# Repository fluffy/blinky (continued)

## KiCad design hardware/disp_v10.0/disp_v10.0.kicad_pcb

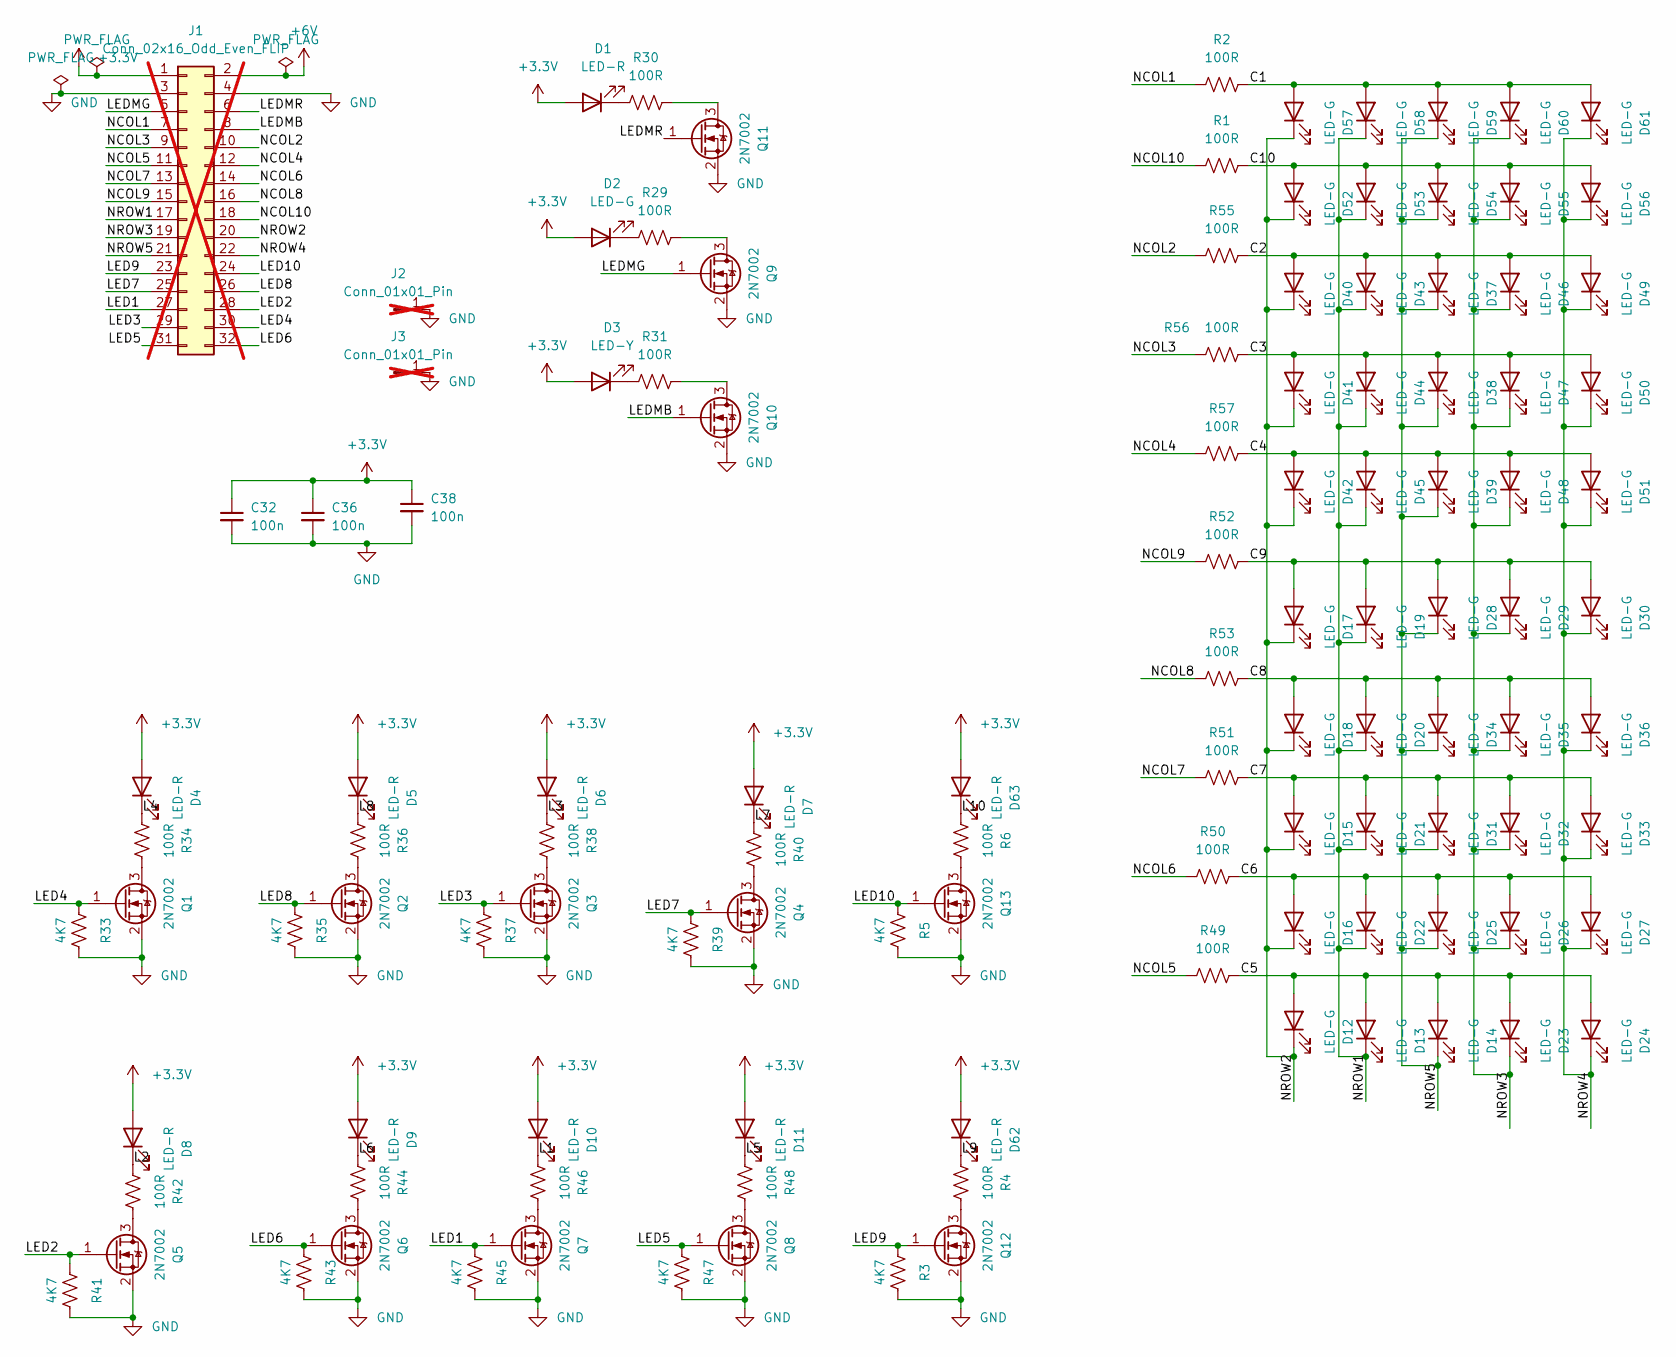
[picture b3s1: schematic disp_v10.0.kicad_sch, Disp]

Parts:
C32, C36, C38: 100n; C_0402_1005Metric; JLCPCB Part # C307331
D1, D4, D5, D6, D7, D8, D9, D10, D11, D62, D63: LED-R; LED_0603_1608Metric; JLCPCB Part # C94869
D2, D12, D13, D14, D15, D16, D17, D18, D19, D20, D21, D22, D23, D24, D25, D26, D27, D28, D29, D30, D31, D32, D33, D34, D35, D36, D37, D38, D39, D40, D41, D42, D43, D44, D45, D46, D47, D48, D49, D50, D51, D52, D53, D54, D55, D56, D57, D58, D59, D60, D61: LED-G; LED_0603_1608Metric; JLCPCB Part # C125093
D3: LED-Y; LED_0603_1608Metric; JLCPCB Part # C72038
J1: Conn_02x16_Odd_Even_FLIP; PinHeader_2x16_P2.54mm_Vertical; not fitted
J2, J3: Conn_01x01_Pin; PinHeader_1x01_P2.54mm_Vertical; not fitted
Q1, Q2, Q3, Q4, Q5, Q6, Q7, Q8, Q9, Q10, Q11, Q12, Q13: 2N7002; SOT-23; JLCPCB Part # C8545
R1, R2, R4, R6, R29, R30, R31, R34, R36, R38, R40, R42, R44, R46, R48, R49, R50, R51, R52, R53, R55, R56, R57: 100R; R_0603_1608Metric; JLCPCB Part # C22775
R3, R5, R33, R35, R37, R39, R41, R43, R45, R47: 4K7; R_0603_1608Metric; JLCPCB Part # C23162

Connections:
+3.3V: C32.1, C36.1, C38.1, D1.2 (A), D2.2 (A), D3.2 (A), D4.2 (A), D5.2 (A), D6.2 (A), D7.2 (A), D8.2 (A), D9.2 (A), D10.2 (A), D11.2 (A), D62.2 (A), D63.2 (A), J1.1
+6V: J1.2
/C1: D57.2 (A), D58.2 (A), D59.2 (A), D60.2 (A), D61.2 (A), R2.1
/C2: D37.2 (A), D40.2 (A), D43.2 (A), D46.2 (A), D49.2 (A), R55.1
/C3: D38.2 (A), D41.2 (A), D44.2 (A), D47.2 (A), D50.2 (A), R56.1
/C4: D39.2 (A), D42.2 (A), D45.2 (A), D48.2 (A), D51.2 (A), R57.1
/C5: D12.2 (A), D13.2 (A), D14.2 (A), D23.2 (A), D24.2 (A), R49.1
/C6: D16.2 (A), D22.2 (A), D25.2 (A), D26.2 (A), D27.2 (A), R50.1
/C7: D15.2 (A), D21.2 (A), D31.2 (A), D32.2 (A), D33.2 (A), R51.1
/C8: D18.2 (A), D20.2 (A), D34.2 (A), D35.2 (A), D36.2 (A), R53.1
/C9: D17.2 (A), D19.2 (A), D28.2 (A), D29.2 (A), D30.2 (A), R52.1
/C10: D52.2 (A), D53.2 (A), D54.2 (A), D55.2 (A), D56.2 (A), R1.1
/L1: D10.1 (K), R46.1
/L2: D8.1 (K), R42.1
/L3: D6.1 (K), R38.1
/L4: D4.1 (K), R34.1
/L5: D11.1 (K), R48.1
/L6: D9.1 (K), R44.1
/L7: D7.1 (K), R40.1
/L8: D5.1 (K), R36.1
/L9: D62.1 (K), R4.1
/L10: D63.1 (K), R6.1
/LED1: J1.27, Q7.1 (G), R45.2
/LED2: J1.28, Q5.1 (G), R41.2
/LED3: J1.29, Q3.1 (G), R37.2
/LED4: J1.30, Q1.1 (G), R33.2
/LED5: J1.31, Q8.1 (G), R47.2
/LED6: J1.32, Q6.1 (G), R43.2
/LED7: J1.25, Q4.1 (G), R39.2
/LED8: J1.26, Q2.1 (G), R35.2
/LED9: J1.23, Q12.1 (G), R3.2
/LED10: J1.24, Q13.1 (G), R5.2
/LEDMB: J1.8, Q10.1 (G)
/LEDMG: J1.5, Q9.1 (G)
/LEDMR: J1.6, Q11.1 (G)
/NCOL1: J1.7, R2.2
/NCOL2: J1.10, R55.2
/NCOL3: J1.9, R56.2
/NCOL4: J1.12, R57.2
/NCOL5: J1.11, R49.2
/NCOL6: J1.14, R50.2
/NCOL7: J1.13, R51.2
/NCOL8: J1.16, R53.2
/NCOL9: J1.15, R52.2
/NCOL10: J1.18, R1.2
/NROW1: D13.1 (K), D19.1 (K), D20.1 (K), D21.1 (K), D22.1 (K), D43.1 (K), D44.1 (K), D45.1 (K), D53.1 (K), D58.1 (K), J1.17
/NROW2: D12.1 (K), D15.1 (K), D16.1 (K), D17.1 (K), D18.1 (K), D40.1 (K), D41.1 (K), D42.1 (K), D52.1 (K), D57.1 (K), J1.20
/NROW3: D23.1 (K), D26.1 (K), D29.1 (K), D32.1 (K), D35.1 (K), D46.1 (K), D47.1 (K), D48.1 (K), D55.1 (K), D60.1 (K), J1.19
/NROW4: D24.1 (K), D27.1 (K), D30.1 (K), D33.1 (K), D36.1 (K), D49.1 (K), D50.1 (K), D51.1 (K), D56.1 (K), D61.1 (K), J1.22
/NROW5: D14.1 (K), D25.1 (K), D28.1 (K), D31.1 (K), D34.1 (K), D37.1 (K), D38.1 (K), D39.1 (K), D54.1 (K), D59.1 (K), J1.21
GND: C32.2, C36.2, C38.2, J1.3, J1.4, J2.1, J3.1, Q1.2 (S), Q2.2 (S), Q3.2 (S), Q4.2 (S), Q5.2 (S), Q6.2 (S), Q7.2 (S), Q8.2 (S), Q9.2 (S), Q10.2 (S), Q11.2 (S), Q12.2 (S), Q13.2 (S), R3.1, R5.1, R33.1, R35.1, R37.1, R39.1, R41.1, R43.1, R45.1, R47.1
unnamed: D1.1 (K), R30.1
unnamed: D2.1 (K), R29.1
unnamed: D3.1 (K), R31.1
unnamed: Q1.3 (D), R34.2
unnamed: Q2.3 (D), R36.2
unnamed: Q3.3 (D), R38.2
unnamed: Q4.3 (D), R40.2
unnamed: Q5.3 (D), R42.2
unnamed: Q6.3 (D), R44.2
unnamed: Q7.3 (D), R46.2
unnamed: Q8.3 (D), R48.2
unnamed: Q9.3 (D), R29.2
unnamed: Q10.3 (D), R31.2
unnamed: Q11.3 (D), R30.2
unnamed: Q12.3 (D), R4.2
unnamed: Q13.3 (D), R6.2

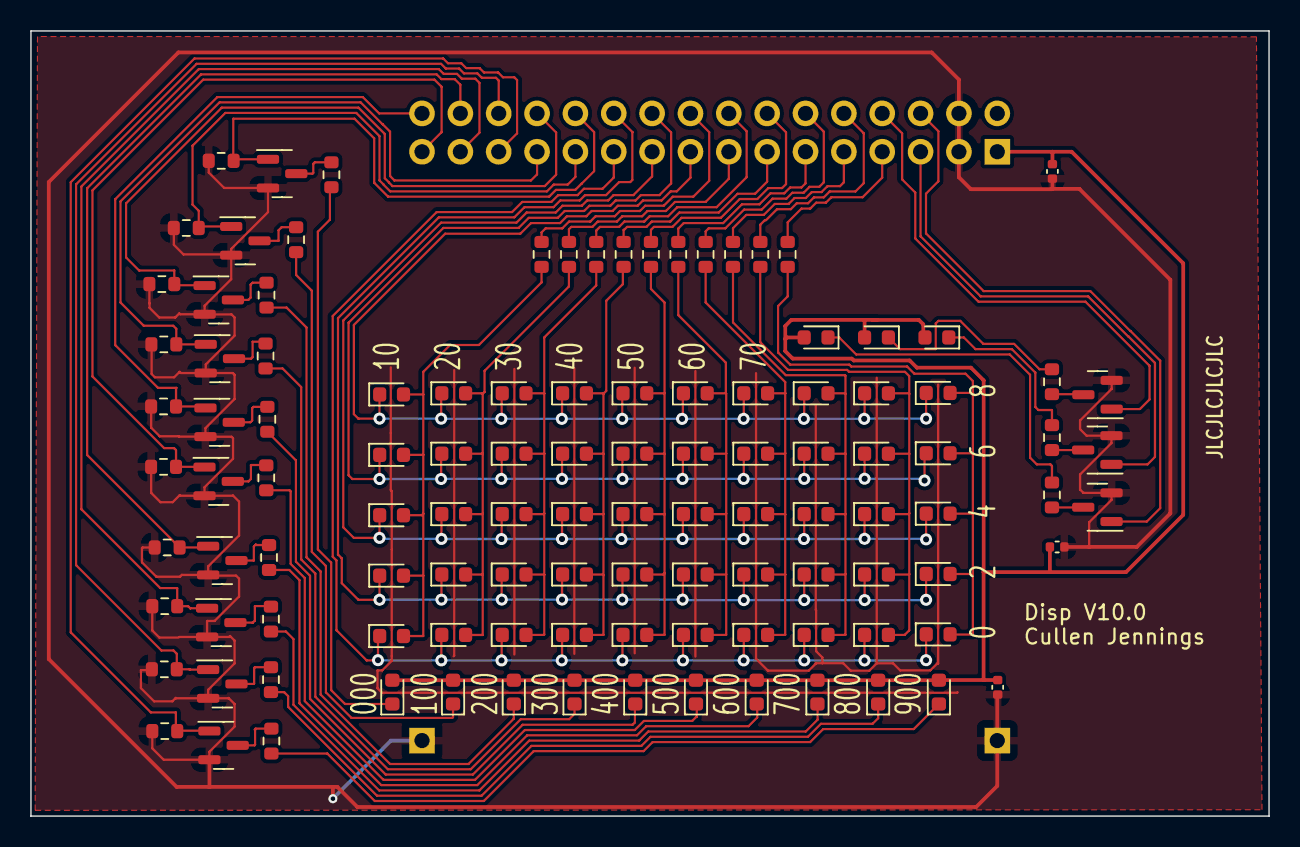
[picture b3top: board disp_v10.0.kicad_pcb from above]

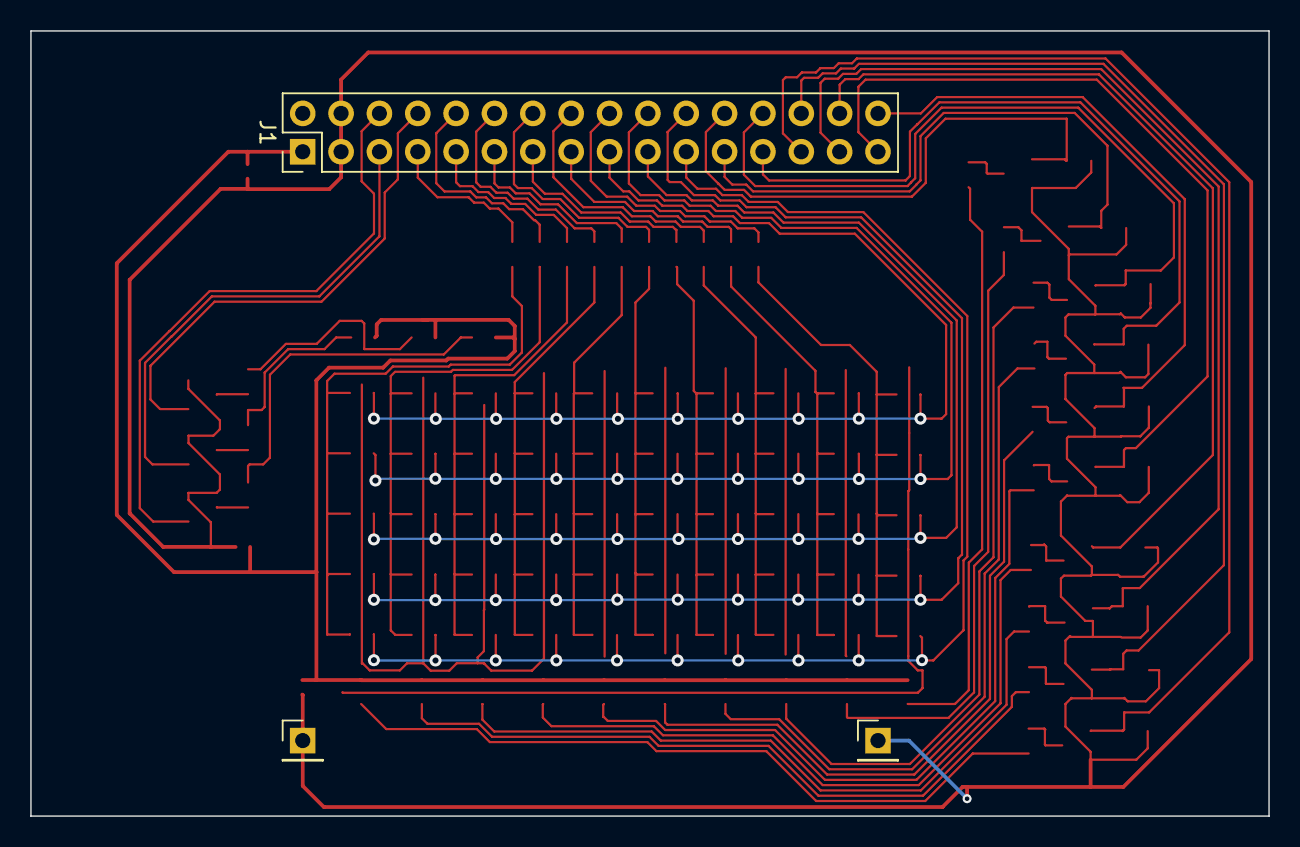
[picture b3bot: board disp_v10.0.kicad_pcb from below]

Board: 2 copper layers, 82.0 x 52.0 mm, 115 parts (3 on the bottom side), 66 nets.

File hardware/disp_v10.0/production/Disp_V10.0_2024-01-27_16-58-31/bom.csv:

Designator,Footprint,Quantity,Value,LCSC Part #
"C32, C36, C38",0402,3,100n,C307331
"D1, D10, D11, D4, D5, D6, D62, D63, D7, D8, D9",0603,11,LED-R,C94869
"D12, D13, D14, D15, D16, D17, D18, D19, D2, D20, D21, D22, D23, D24, D25, D26, D27, D28, D29, D30, D31, D32, D33, D34, D35, D36, D37, D38, D39, D40, D41, D42, D43, D44, D45, D46, D47, D48, D49, D50, D51, D52, D53, D54, D55, D56, D57, D58, D59, D60, D61",0603,51,LED-G,C125093
D3,0603,1,LED-Y,C72038
"Q1, Q10, Q11, Q12, Q13, Q2, Q3, Q4, Q5, Q6, Q7, Q8, Q9",SOT-23,13,2N7002,C8545
"R1, R2, R29, R30, R31, R34, R36, R38, R4, R40, R42, R44, R46, R48, R49, R50, R51, R52, R53, R55, R56, R57, R6",0603,23,100R,C22775
"R3, R33, R35, R37, R39, R41, R43, R45, R47, R5",0603,10,4K7,C23162

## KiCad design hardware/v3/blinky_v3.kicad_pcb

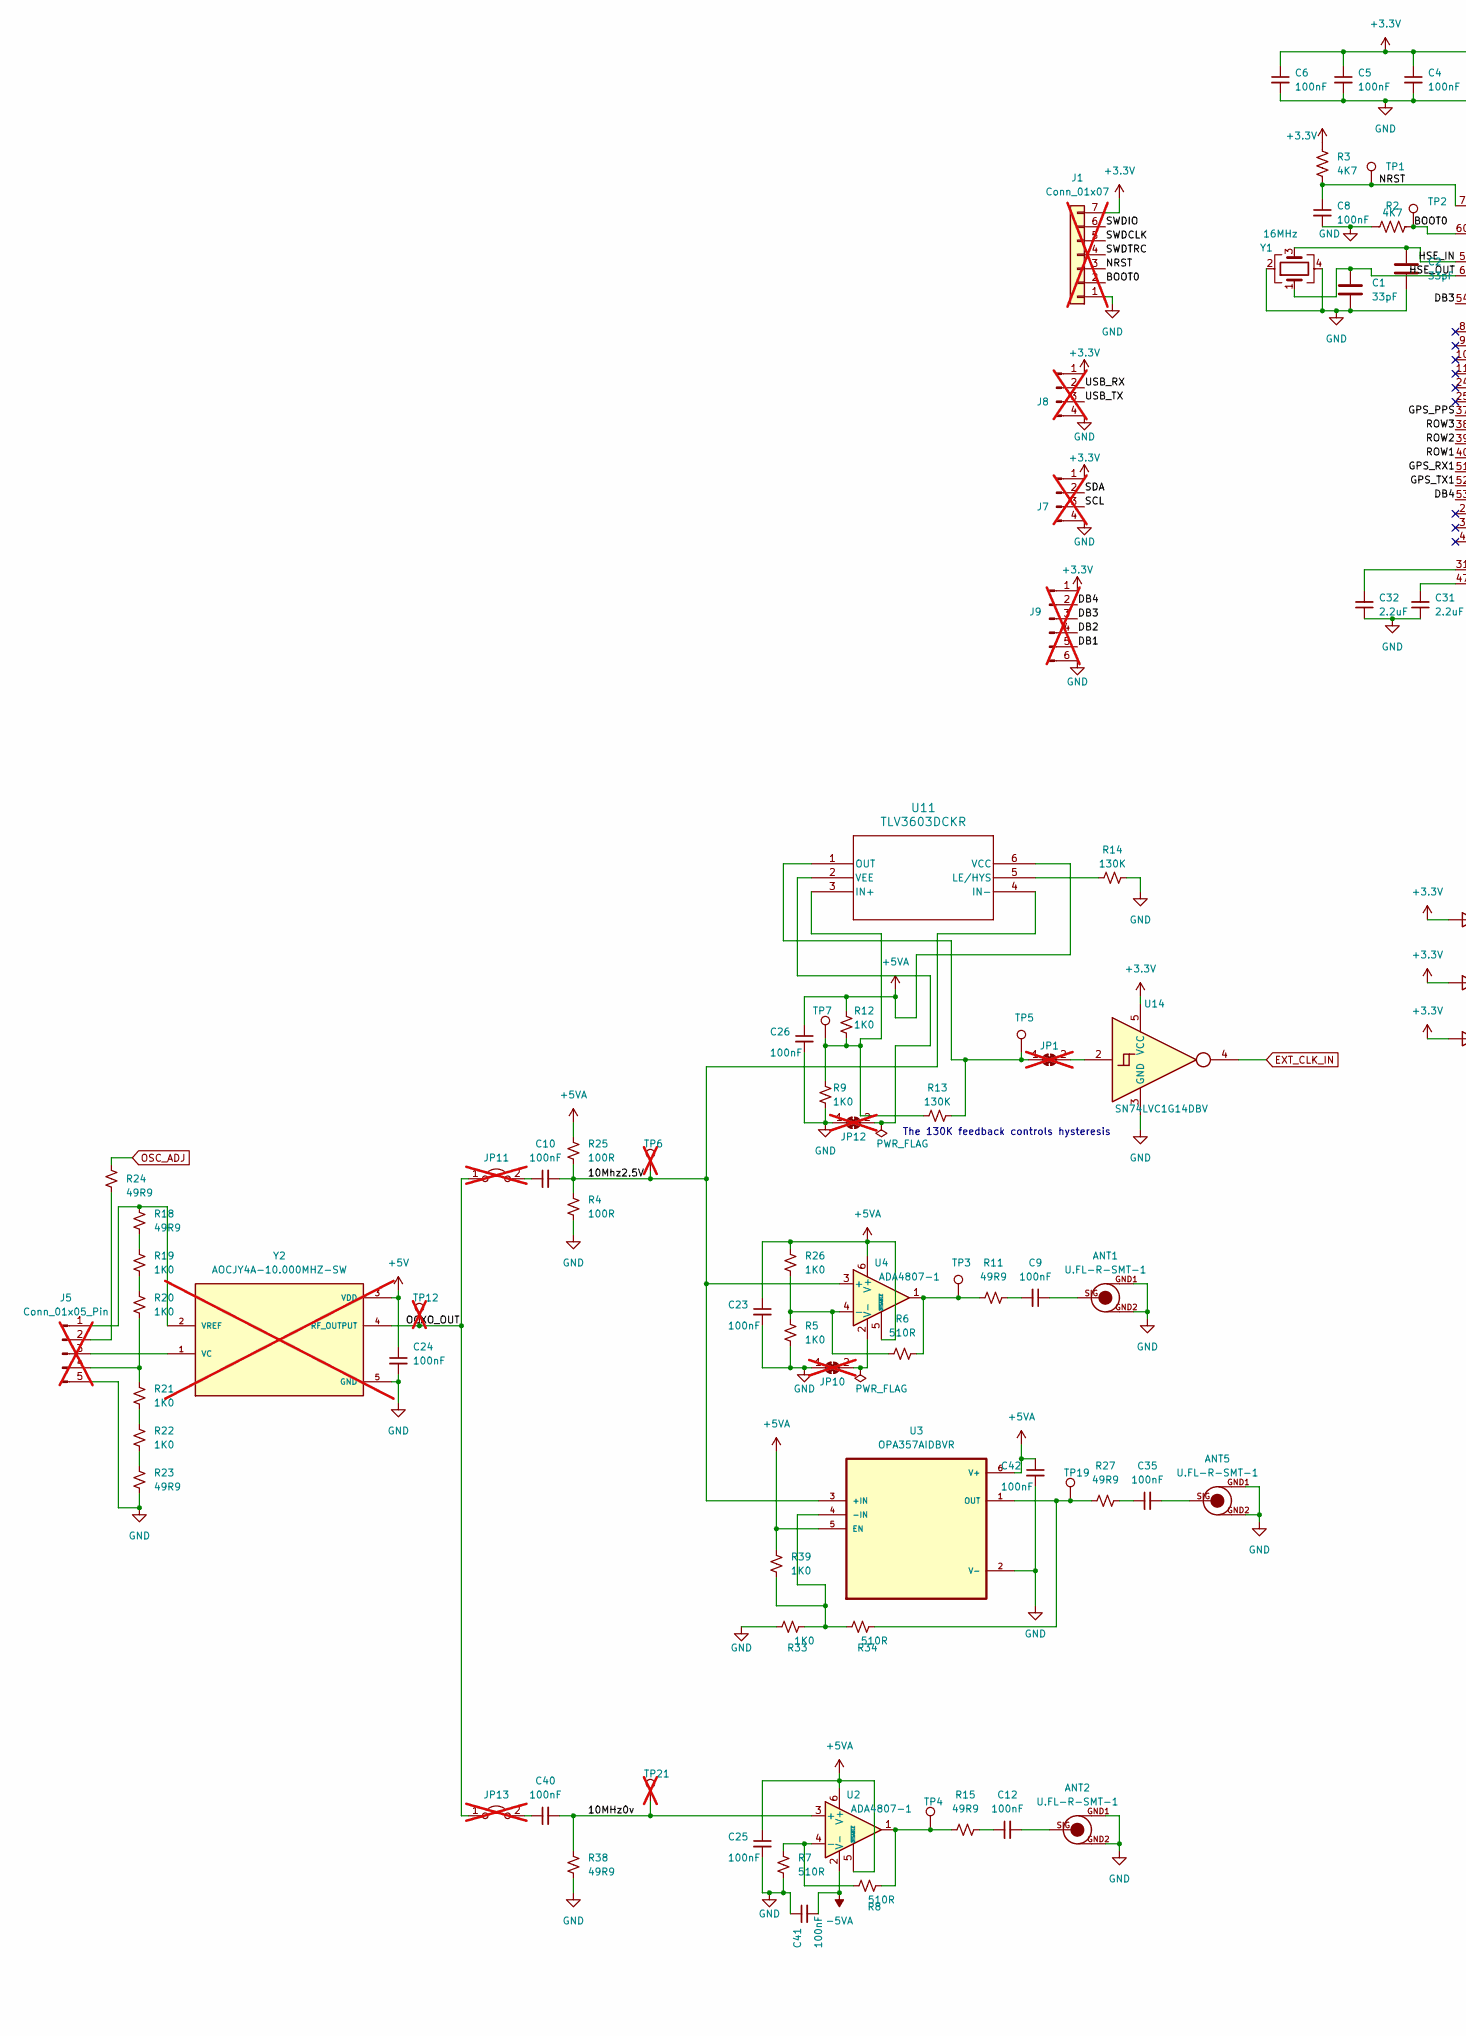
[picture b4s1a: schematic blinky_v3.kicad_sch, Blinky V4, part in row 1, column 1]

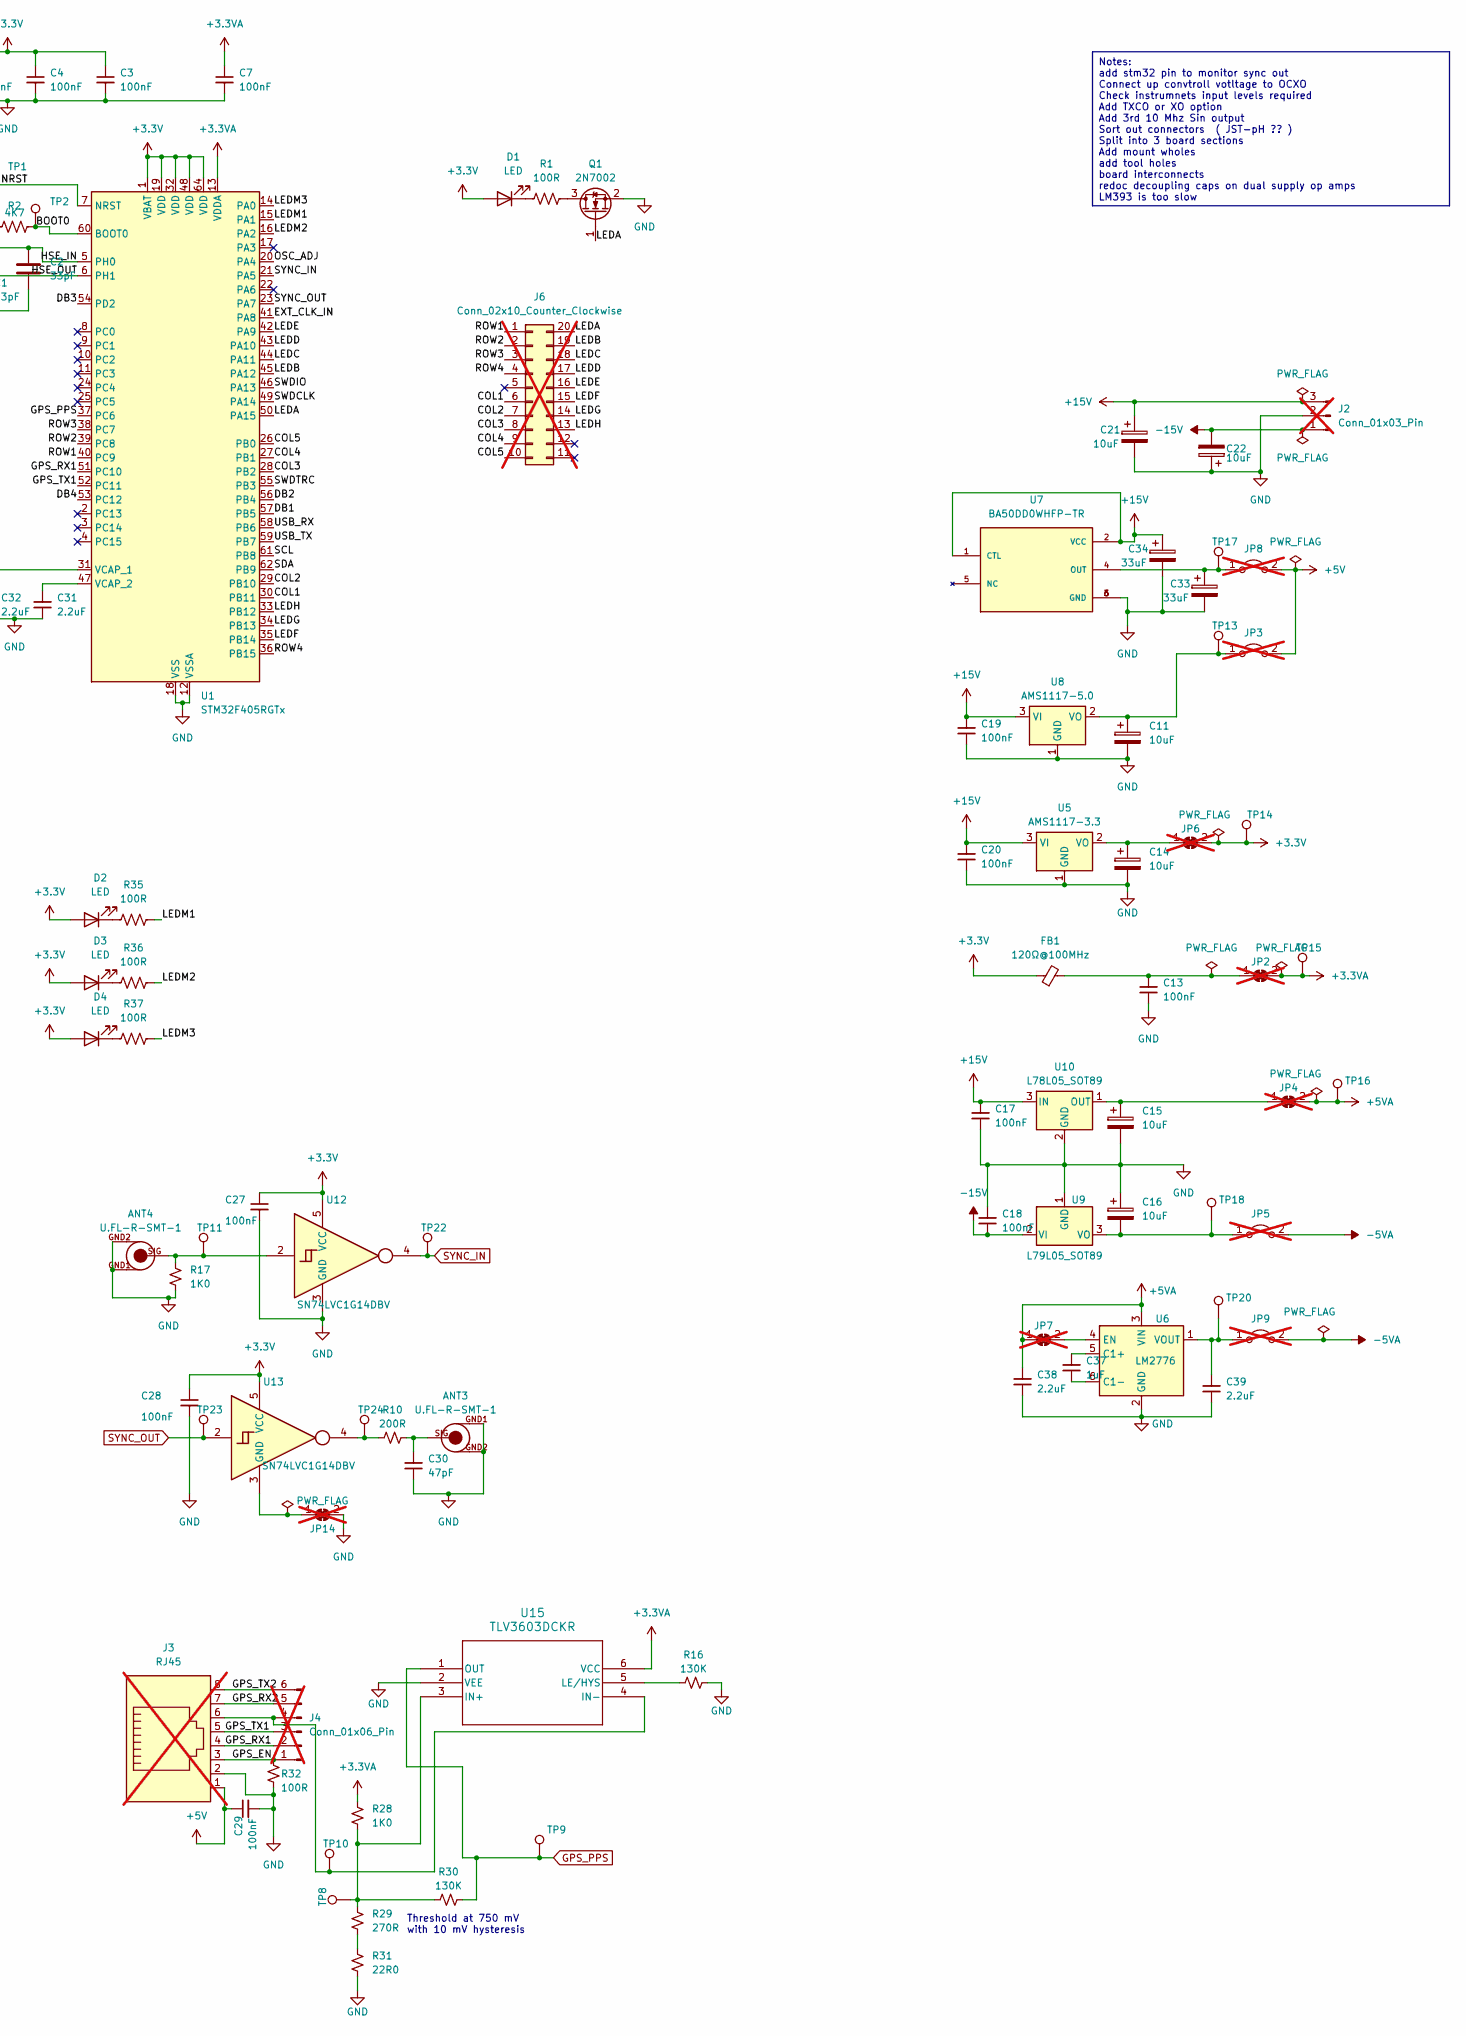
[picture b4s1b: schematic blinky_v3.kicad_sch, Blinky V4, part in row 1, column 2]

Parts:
ANT1, ANT2, ANT3, ANT4, ANT5: U.FL-R-SMT-1; LCSC C88374
C1, C2: 33pF; C_0603_1608Metric; LCSC C1663
C3, C4, C5, C6, C7, C17, C18, C19, C20, C23, C24, C25, C26, C27, C28, C29, C41, C42: 100nF; C_0402_1005Metric; LCSC C307331
C8, C9, C10, C12, C13, C35, C40: 100nF; C_0603_1608Metric; LCSC C14663
C11, C14, C15, C16, C21, C22: 10uF; CP_EIA-3216-18_Kemet-A; LCSC C7171
C30: 47pF; C_0805_2012Metric; LCSC C14857
C31, C32, C38, C39: 2.2uF; C_0603_1608Metric; LCSC C23630
C33, C34: 33uF; CP_EIA-3528-21_Kemet-B; LCSC C128342
C37: 1uF; C_0603_1608Metric; LCSC C15849
D1, D2, D3, D4: LED; R_0603_1608Metric; LCSC C94869
FB1: 120Ω@100MHz; R_0603_1608Metric; LCSC C127301
J1: Conn_01x07; PinHeader_1x07_P2.54mm_Vertical; not fitted
J2: Conn_01x03_Pin; PinHeader_1x03_P2.54mm_Vertical; not fitted
J3: RJ45; RJ45_Amphenol_RJHSE5380; LCSC C464586; not fitted
J4, J9: Conn_01x06_Pin; PinHeader_1x06_P2.54mm_Vertical; not fitted
J5: Conn_01x05_Pin; PinHeader_1x05_P2.54mm_Vertical; not fitted
J6: Conn_02x10_Counter_Clockwise; PinHeader_2x10_P2.54mm_Vertical; not fitted
J7, J8: Conn_01x04_Pin; PinHeader_1x04_P2.54mm_Vertical; not fitted
JP1, JP2, JP4, JP6, JP7, JP10, JP12, JP14: SolderJumper_2_Bridged; SolderJumper-2_P1.3mm_Bridged_RoundedPad1.0x1.5mm; not fitted
JP3, JP5, JP8, JP9, JP11, JP13: TestPoint_2Pads_Pitch2.54mm_Drill0.8mm; not fitted
Q1: 2N7002; SOT-23; LCSC C8545
R1, R4, R25, R32, R35, R36, R37: 100R; R_0603_1608Metric; LCSC C22775
R2, R3: 4K7; R_0603_1608Metric; LCSC C23162
R5, R9, R12, R17, R26, R28, R33, R39: 1K0; R_0603_1608Metric; LCSC C21190
R6, R7, R8, R34: 510R; R_0603_1608Metric; LCSC C23193
R10: 200R; R_0805_2012Metric; LCSC C17540
R11, R15, R18, R23, R24, R27, R38: 49R9; R_0805_2012Metric; LCSC C17720
R13, R14, R16, R30: 130K; R_0603_1608Metric; LCSC C22795
R19, R20, R21, R22: 1K0; R_0805_2012Metric; LCSC C21190
R29: 270R; R_0603_1608Metric; LCSC C22966
R31: 22R0; R_0603_1608Metric; LCSC C23345
TP1, TP2, TP3, TP4, TP5, TP7, TP8, TP9, TP10, TP11, TP13, TP14, TP15, TP16, TP17, TP18, TP19, TP20, TP22, TP23, TP24: TestPoint_THTPad_D1.5mm_Drill0.7mm
TP6, TP12, TP21: TestPoint_THTPad_D1.5mm_Drill0.7mm; not fitted
U1: STM32F405RGTx; LQFP-64_10x10mm_P0.5mm; LCSC C15742
U2, U4: ADA4807-1; SOT-23-6; LCSC C2058411
U3: OPA357AIDBVR; SOT95P280X145-6N; LCSC C139385
U5: AMS1117-3.3; SOT-223-3_TabPin2; LCSC C6186
U6: LM2776; SOT-23-6; LCSC C69527
U7: BA50DD0WHFP-TR; DPAK172P1054X200-6N; PARTREV 003; LCSC C509718
U8: AMS1117-5.0; SOT-223-3_TabPin2; LCSC C6187
U9: L79L05_SOT89; SOT-89-3; LCSC C122849
U10: L78L05_SOT89; SOT-89-3; LCSC C71136
U11, U15: TLV3603DCKR; SC70_DCK_TEX; LCSC C5213955
U12, U13, U14: SN74LVC1G14DBV; SOT-23-5; LCSC C133145
Y1: 16MHz; Crystal_SMD_3225-4Pin_3.2x2.5mm; LCSC C13738
Y2: AOCJY4A-10.000MHZ-SW; XTAL_AOCJY4A-10.000MHZ-SW; PARTREV 07.24.11; LCSC C1670487; not fitted

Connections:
+3.3V: C3.1, C4.1, C5.1, C6.1, C27.1, C28.1, D1.2 (A), D2.2 (A), D3.2 (A), D4.2 (A), FB1.1, J1.7, J7.1, J8.1, J9.1, JP6.2 (B), R3.1, TP14.1, U1.1 (VBAT), U1.19 (VDD), U1.32 (VDD), U1.48 (VDD), U1.64 (VDD), U12.5 (VCC), U13.5 (VCC), U14.5 (VCC)
+3.3VA: C7.1, JP2.2 (B), R28.1, TP15.1, U1.13 (VDDA), U15.6 (VCC)
+5V: C24.1, C29.1, J3.1, JP3.2 (B), JP8.2 (B), Y2.3 (VDD)
+5VA: C23.1, C25.1, C26.1, C38.2, C42.1, JP4.2 (B), JP7.1 (A), R12.1, R25.1, R26.1, R39.1, TP16.1, U2.5 (~DISABLE), U2.6 (V+), U3.5 (EN), U3.6 (V+), U4.5 (~DISABLE), U4.6 (V+), U6.3 (VIN), U11.6 (VCC)
+15V: C17.2, C19.2, C20.2, C21.1, C34.1, J2.3, U5.3 (VI), U7.1 (CTL), U7.2 (VCC), U8.3 (VI), U10.3 (IN)
-5VA: C41.2, JP5.2 (B), JP9.2 (B), U2.2 (V-)
-15V: C18.1, C22.2, J2.1, U9.2 (VI)
/10MHz0v: C40.2, R38.1, TP21.1, U2.3 (+)
/10Mhz2.5V: C10.2, R4.1, R25.2, TP6.1, U3.3 (+IN), U4.3 (+), U11.4 (IN-)
/BOOT0: J1.2, R2.1, TP2.1, U1.60 (BOOT0)
/COL1: J6.6, U1.30 (PB11)
/COL2: J6.7, U1.29 (PB10)
/COL3: J6.8, U1.28 (PB2)
/COL4: J6.9, U1.27 (PB1)
/COL5: J6.10, U1.26 (PB0)
/DB1: J9.5, U1.57 (PB5)
/DB2: J9.4, U1.56 (PB4)
/DB3: J9.3, U1.54 (PD2)
/DB4: J9.2, U1.53 (PC12)
/GPS_EN: J3.3, J4.1, R32.1
/GPS_RX1: J3.4, J4.2, U1.51 (PC10)
/GPS_RX2: J3.7, J4.5
/GPS_TX1: J3.5, J4.3, U1.52 (PC11)
/GPS_TX2: J3.8, J4.6
/HSE_IN: C2.1, U1.5 (PH0), Y1.3
/HSE_OUT: C1.1, U1.6 (PH1), Y1.1
/LEDA: J6.20, Q1.1 (G), U1.50 (PA15)
/LEDB: J6.19, U1.45 (PA12)
/LEDC: J6.18, U1.44 (PA11)
/LEDD: J6.17, U1.43 (PA10)
/LEDE: J6.16, U1.42 (PA9)
/LEDF: J6.15, U1.35 (PB14)
/LEDG: J6.14, U1.34 (PB13)
/LEDH: J6.13, U1.33 (PB12)
/LEDM1: R35.2, U1.15 (PA1)
/LEDM2: R36.2, U1.16 (PA2)
/LEDM3: R37.2, U1.14 (PA0)
/NRST: C8.1, J1.3, R3.2, TP1.1, U1.7 (NRST)
/OCXO_OUT: JP11.1 (A), JP13.1 (A), TP12.1, Y2.4 (RF_OUTPUT)
/ROW1: J6.1, U1.40 (PC9)
/ROW2: J6.2, U1.39 (PC8)
/ROW3: J6.3, U1.38 (PC7)
/ROW4: J6.4, U1.36 (PB15)
/SCL: J7.3, U1.61 (PB8)
/SDA: J7.2, U1.62 (PB9)
/SWDCLK: J1.5, U1.49 (PA14)
/SWDIO: J1.6, U1.46 (PA13)
/SWDTRC: J1.4, U1.55 (PB3)
/USB_RX: J8.2, U1.58 (PB6)
/USB_TX: J8.3, U1.59 (PB7)
EXT_CLK_IN: U1.41 (PA8), U14.4
GND: ANT1.GND1, ANT1.GND2, ANT2.GND1, ANT2.GND2, ANT3.GND1, ANT3.GND2, ANT4.GND1, ANT4.GND2, ANT5.GND1, ANT5.GND2, C1.2, C2.2, C3.2, C4.2, C5.2, C6.2, C7.2, C8.2, C11.2, C13.1, C14.2, C15.2, C16.1, C17.1, C18.2, C19.1, C20.1, C21.2, C22.1, C23.2, C24.2, C25.2, C26.2, C27.2, C28.2, C29.2, C30.1, C31.1, C32.1, C33.2, C34.2, C38.1, C39.1, C41.1, C42.2, J1.1, J2.2, J3.2, J5.5, J7.4, J8.4, J9.6, JP10.1 (A), JP12.1 (A), JP14.2 (B), Q1.2 (S), R2.2, R4.2, R5.2, R7.2, R9.2, R14.2, R16.2, R17.2, R23.2, R31.2, R32.2, R33.1, R38.2, U1.12 (VSSA), U1.18 (VSS), U1.63 (VSS), U3.2 (V-), U5.1 (GND), U6.2 (GND), U7.3 (GND), U7.6 (GND), U8.1 (GND), U9.1 (GND), U10.2 (GND), U12.3 (GND), U14.3 (GND), U15.2 (VEE), Y1.2, Y1.4, Y2.5 (GND)
GPS_PPS: R30.2, TP9.1, U1.37 (PC6), U15.1 (OUT)
unnamed: ANT1.SIG, C9.1
unnamed: ANT2.SIG, C12.2
unnamed: ANT3.SIG, C30.2, R10.2
unnamed: ANT4.SIG, R17.1, TP11.1, U12.2
unnamed: ANT5.SIG, C35.2
unnamed: C9.2, R11.2
unnamed: C12.1, R15.2
unnamed: C35.1, R27.2
unnamed: D1.1 (K), R1.1
unnamed: D2.1 (K), R35.1
unnamed: D3.1 (K), R36.1
unnamed: D4.1 (K), R37.1
unnamed: J3.6, J4.4, TP10.1, U15.4 (IN-)
unnamed: J5.1, R18.1, Y2.2 (VREF)
unnamed: J5.2, R24.2
unnamed: J5.3, Y2.1 (VC)
unnamed: J5.4, R20.2, R21.1
unnamed: JP1.1 (A), R13.2, TP5.1, U11.1 (OUT)
unnamed: JP1.2 (B), U14.2
unnamed: C13.2, FB1.2, JP2.1 (A)
unnamed: C11.1, JP3.1 (A), TP13.1, U8.2 (VO)
unnamed: C15.1, JP4.1 (A), U10.1 (OUT)
unnamed: C16.2, JP5.1 (A), TP18.1, U9.3 (VO)
unnamed: C14.1, JP6.1 (A), U5.2 (VO)
unnamed: JP7.2 (B), U6.4 (EN)
unnamed: C33.1, JP8.1 (A), TP17.1, U7.4 (OUT)
unnamed: C39.2, JP9.1 (A), TP20.1, U6.1 (VOUT)
unnamed: JP10.2 (B), U4.2 (V-)
unnamed: C10.1, JP11.2 (B)
unnamed: JP12.2 (B), U11.2 (VEE)
unnamed: C40.1, JP13.2 (B)
unnamed: JP14.1 (A), U13.3 (GND)
unnamed: Q1.3 (D), R1.2
unnamed: R10.1, TP24.1, U13.4
unnamed: R6.2, R11.1, TP3.1, U4.1
unnamed: R8.2, R15.1, TP4.1, U2.1
unnamed: R18.2, R19.1
unnamed: R19.2, R20.1
unnamed: R21.2, R22.1
unnamed: R22.2, R23.1
unnamed: R29.2, R31.1
unnamed: C32.2, U1.31 (VCAP_1)
unnamed: C31.2, U1.47 (VCAP_2)
unnamed: R7.1, R8.1, U2.4 (-)
unnamed: R33.2, R34.1, R39.2, U3.4 (-IN)
unnamed: R27.1, R34.2, TP19.1, U3.1 (OUT)
unnamed: R5.1, R6.1, R26.2, U4.4 (-)
unnamed: C37.2, U6.5 (C1+)
unnamed: C37.1, U6.6 (C1-)
unnamed: R9.1, R12.2, R13.1, TP7.1, U11.3 (IN+)
unnamed: R14.1, U11.5 (LE/HYS)
unnamed: R28.2, R29.1, R30.1, TP8.1, U15.3 (IN+)
unnamed: R16.1, U15.5 (LE/HYS)
OSC_ADJ: R24.1, U1.20 (PA4)
SYNC_IN: TP22.1, U1.21 (PA5), U12.4
SYNC_OUT: TP23.1, U1.23 (PA7), U13.2

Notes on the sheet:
Notes: add stm32 pin to monitor sync out Connect up convtroll votltage to OCXO Check instrumnets input levels required Add TXCO or XO option Add 3rd 10 Mhz Sin output Sort out connectors ( JST-pH ?? ) Split into 3 board sections Add mount wholes add tool holes board interconnects redoc decoupling c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
Threshold at 750 mV with 10 mV hysteresis
The 130K feedback controls hysteresis

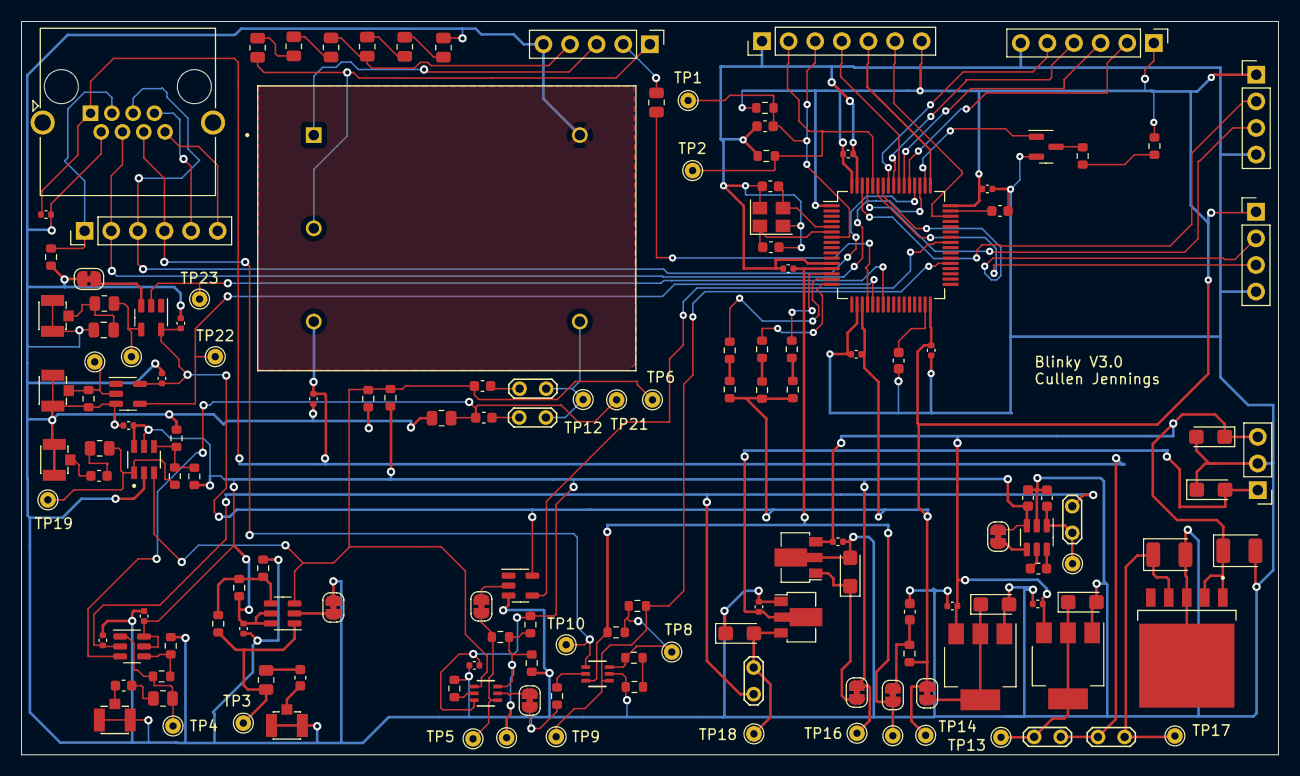
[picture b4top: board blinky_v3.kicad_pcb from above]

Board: 2 copper layers, 120.0 x 70.0 mm, 154 parts (0 on the bottom side), 93 nets.
